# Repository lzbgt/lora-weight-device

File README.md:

# Hospital Urine Bag Monitoring System (LoRaWAN)

## Project Overview
A low-power, connected IoT device designed to automatically monitor urine output in hospital wards. It replaces manual visual checks with real-time digital logging, improving patient care and reducing nurse workload.

**Key Features:**
*   **Sensing:** Weight-based (Load Cell) for non-contact, universal bag compatibility.
*   **Connectivity:** **LoRaWAN** (Sub-1GHz) for deep indoor penetration and low infrastructure cost (1 gateway per ward).
*   **Battery Life:** Multi-year operation on AA batteries or Li-SoCl2.
*   **User Interface:** E-Ink Display for always-on visibility and local "Tare" button.
*   **Infrastructure:** Supports both **PoE** and **Wi-Fi** backhaul for the Gateway.

## Repository Structure

### Design Documents (`design_docs/`)
*   **`system_architecture.md`**: High-level topology, data flow, and server stack (ChirpStack).
*   **`hardware_design.md`**: Schematic concepts, chip selection (RAK3172, HX711), and detailed pin mapping.
*   **`mechanical_design.md`**: Enclosure styling, IP65 sealing, and the miniature load cell integration (Hook mechanism).
*   **`firmware_design.md`**: Software logic, state machine (Deep Sleep), and LoRaWAN payload format.
*   **`pcb_layout_guide.md`**: Critical routing rules for RF impedance and Analog noise reduction.
*   **`detailed_bom.md`**: Bill of Materials with part numbers and cost estimates.
*   **`solution_proposal.md`**: original proposal.

### Datasheets (`datasheets/`)
Contains reference specifications for critical components:
*   **RAK3172**: LoRaWAN Module.
*   **GDEY0213B74**: 2.13" E-Ink Display.
*   **HX711**: 24-Bit ADC.
*   **SSD1680**: Display Controller (Command Table).

## Getting Started

### 1. Hardware Development
*   Review `hardware_design.md` for the schematic connectivity.
*   Follow `pcb_layout_guide.md` for board layout, paying special attention to the **50Ω RF Trace** and **E-Ink Booster** loop.
*   Ensure the **Schottky Diode OR-ing** is implemented to protect the 3.3V rail.

### 2. Firmware Development
*   **Toolchain:** STM32CubeWL SDK + CMake + GCC ARM.
*   **Key Logic:** Implement the "Deep Sleep Loop" (Wait 400ms for HX711 -> Read -> Sleep).
*   **Display:** Use the SSD1680 driver with the specific bias voltages (+20V/-20V/+15V/-15V) defined in the hardware spec.

### 3. Mechanical Prototyping
*   Design the enclosure to fit the **Miniature Load Cell** (40mm).
*   Ensure the **Tube Retention Clip** is molded into the front shell to prevent measurement errors.

## License
Proprietary / Internal Company Use.

## Commercial support

For teams adapting this repo for ESP32, Bluetooth, Wi-Fi provisioning, LoRa/LoRaWAN, low-power sensing, gateway handoff, or prototype-to-pilot embedded device work, I offer a paid bring-up review:

- Review page: https://x2.brucelu.top/iot/?source=github-lora-weight-device
- Sample deliverable: https://x2.brucelu.top/iot/sample/
- Checkout: https://x2.brucelu.top/iot/checkout/?source=github-lora-weight-device
- Product catalog: https://x2.brucelu.top/products/?source=github-lora-weight-device

Boundary: this is paid engineering review/support. It does not include medical/regulatory approval, guaranteed RF range, hardware repair, credential-managed operation, or custom firmware delivery.

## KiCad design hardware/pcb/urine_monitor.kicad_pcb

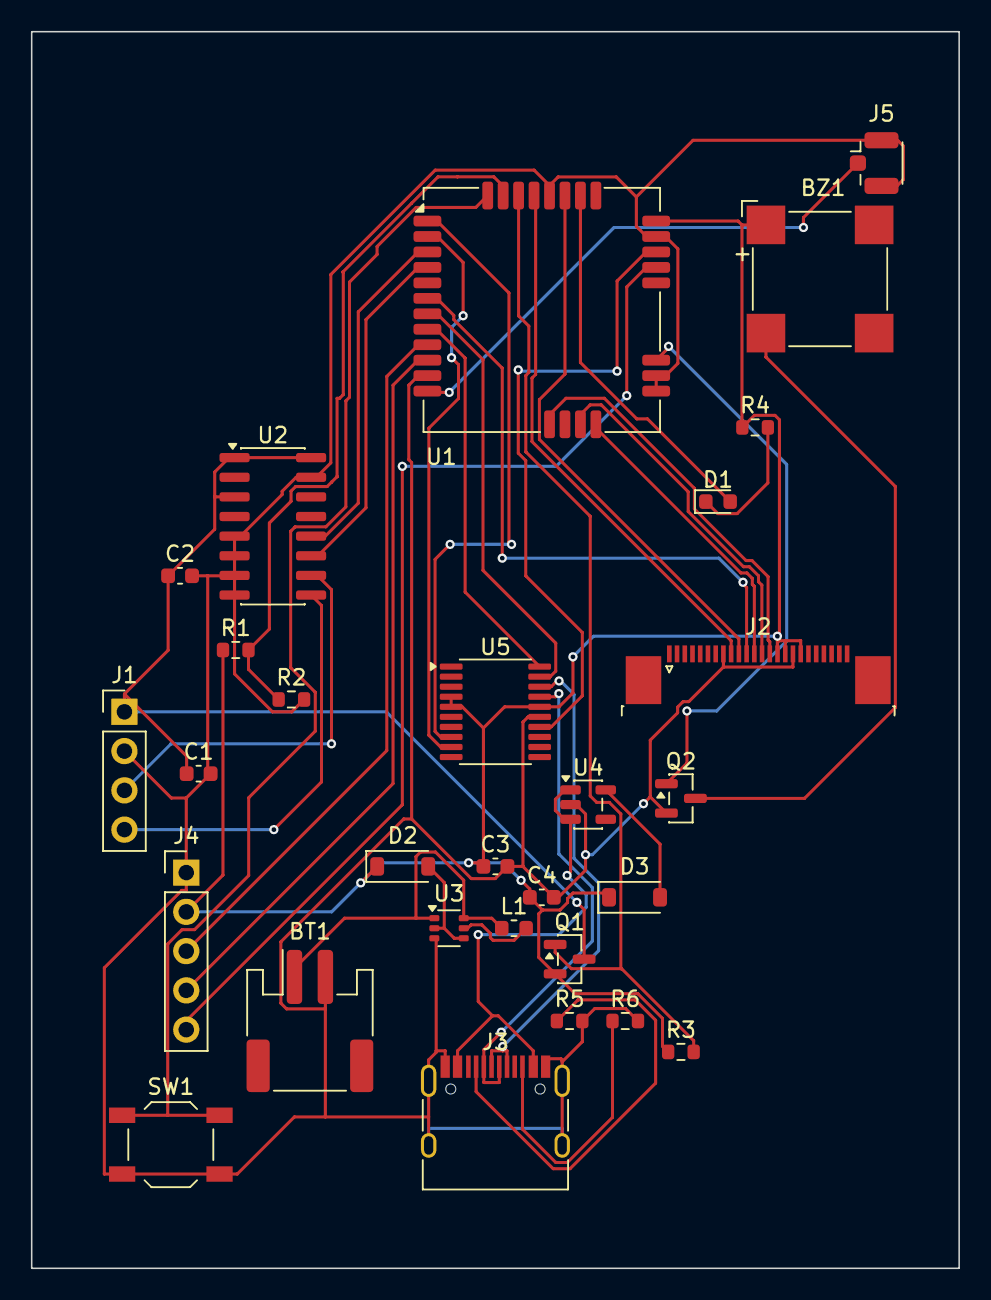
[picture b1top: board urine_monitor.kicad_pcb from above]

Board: 2 copper layers, 60.0 x 80.0 mm, 29 parts (0 on the bottom side), 38 nets.

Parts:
BT1: BAT_JST; JST_PH_S2B-PH-SM4-TB_1x02-1MP_P2.00mm_Horizontal
BZ1: Buzzer; MagneticBuzzer_CUI_CMT-8504-100-SMT
C1, C3: 10uF; C_0603_1608Metric
C2, C4: 0.1uF; C_0603_1608Metric
D1: RED; LED_0603_1608Metric
D2, D3: SS14; D_SOD-123
J1: LoadCell; PinHeader_1x04_P2.54mm_Vertical
J2: EInk_FPC; TE_2-1734839-4_1x24-1MP_P0.5mm_Horizontal
J3: USB-C_Dev; USB_C_Receptacle_HRO_TYPE-C-31-M-12
J4: I2C+BOOT0+PWR; PinHeader_1x05_P2.54mm_Vertical
J5: Antenna_UFL; U.FL_Hirose_U.FL-R-SMT-1_Vertical
L1: 4.7uH; L_0603_1608Metric
Q1: SI2301; SOT-23
Q2: 2N7002; SOT-23
R1, R2: 1M; R_0603_1608Metric
R3: 100k; R_0603_1608Metric
R4: 1k; R_0603_1608Metric
R5, R6: 5k1; R_0603_1608Metric
SW1: USER_BTN; SW_SPST_TL3342
U1: RAK3172
U2: HX711; SOIC-16_3.9x9.9mm_P1.27mm
U3: TPS61220; SOT-363_SC-70-6
U4: MIC5504-3.3; SOT-23-5
U5: STM32F042F6P6 (USB CDC + CMSIS-DAP); TSSOP-20_4.4x6.5mm_P0.65mm

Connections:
BAT: BT1.1, L1.1, U3.1, U3.6
BAT_SENSE: R1.2, R2.1, U1.31
BOOT0: J4.5, U1.21
BTN_USER: SW1.1, U1.32
BUZZ_PWM: Q2.1, U1.19
BUZZ_SINK: BZ1.2, Q2.3
CC1: J3.A5, R5.1
CC2: J3.B5, R6.1
EINK_BUSY: J2.9, U1.29
EINK_CS: J2.12, U1.16
EINK_DC: J2.11, U1.6
EINK_MOSI: J2.14, U1.13
EINK_RST: J2.10, U1.27
EINK_SCK: J2.13, U1.15
GND: BT1.2, C1.2, C2.2, C3.2, C4.2, J1.2, J2.8, J2.17, J3.A1, J3.A12, J3.B1, J3.B12, J3.S1, J4.1, J5.2, Q2.2, R2.2, R5.2, R6.2, SW1.2, U1.11, U1.17, U1.18, U1.23, U1.28, U2.5, U2.6, U2.7, U2.8, U2.15, U3.3, U4.2, U5.15
HX711_DT: U1.3, U2.12
HX711_SCK: U1.4, U2.11
HX_GATE: Q1.1, R3.2, U1.30
HX_INB+: J1.3, U2.10
HX_INB-: J1.4, U2.9
HX_VCC: C1.1, C2.1, J1.1, Q1.3, U2.1, U2.3, U2.16
I2C_SCL: J4.3, U1.9
I2C_SDA: J4.4, U1.10
LED_NET: D1.1, R4.2
LED_STATUS: D1.2, U1.26
NRST: U1.22, U5.14
RF: J5.1, U1.12
SWCLK: U1.8, U5.20
SWDIO: U1.7, U5.19
U3_L: L1.2, U3.5
U3_OUT: D2.2, U3.2, U3.4
U4_OUT: D3.2, U4.5
UART2_RX: U1.1, U5.8
UART2_TX: U1.2, U5.9
USB_DM: J3.A7, J3.B7, U5.17
USB_DP: J3.A6, J3.B6, U5.18
VBUS: J3.A4, J3.A9, J3.B4, J3.B9, U4.1, U4.3
VCC: BZ1.1, C3.1, C4.1, D2.1, D3.1, J2.15, J2.16, J2.18, J4.2, Q1.2, R1.1, R3.1, R4.1, U1.24, U5.4, U5.5, U5.16

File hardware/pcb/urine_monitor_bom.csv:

"Refs","Value","Footprint","Qty","DNP"
"BT1","BAT_JST","Connector_JST:JST_PH_S2B-PH-SM4-TB_1x02-1MP_P2.00mm_Horizontal","1",""
"BZ1","Buzzer","Buzzer_Beeper:MagneticBuzzer_CUI_CMT-8504-100-SMT","1",""
"C1","10uF","Capacitor_SMD:C_0603_1608Metric","1",""
"C2","0.1uF","Capacitor_SMD:C_0603_1608Metric","1",""
"C3","10uF","Capacitor_SMD:C_0603_1608Metric","1",""
"C4","0.1uF","Capacitor_SMD:C_0603_1608Metric","1",""
"D1","RED","LED_SMD:LED_0603_1608Metric","1",""
"D2","SS14","Diode_SMD:D_SOD-123","1",""
"D3","SS14","Diode_SMD:D_SOD-123","1",""
"J1","LoadCell","Connector_PinHeader_2.54mm:PinHeader_1x04_P2.54mm_Vertical","1",""
"J2","EInk_FPC","Connector_FFC-FPC:TE_2-1734839-4_1x24-1MP_P0.5mm_Horizontal","1",""
"J3","USB-C_Dev","Connector_USB:USB_C_Receptacle_HRO_TYPE-C-31-M-12","1",""
"J4","I2C+BOOT0+PWR","Connector_PinHeader_2.54mm:PinHeader_1x05_P2.54mm_Vertical","1",""
"J5","Antenna_UFL","Connector_Coaxial:U.FL_Hirose_U.FL-R-SMT-1_Vertical","1",""
"L1","4.7uH","Inductor_SMD:L_0603_1608Metric","1",""
"Q1","SI2301","Package_TO_SOT_SMD:SOT-23","1",""
"Q2","2N7002","Package_TO_SOT_SMD:SOT-23","1",""
"R1","1M","Resistor_SMD:R_0603_1608Metric","1",""
"R2","1M","Resistor_SMD:R_0603_1608Metric","1",""
"R3","100k","Resistor_SMD:R_0603_1608Metric","1",""
"R4","1k","Resistor_SMD:R_0603_1608Metric","1",""
"R5","5k1","Resistor_SMD:R_0603_1608Metric","1",""
"R6","5k1","Resistor_SMD:R_0603_1608Metric","1",""
"SW1","USER_BTN","Button_Switch_SMD:SW_SPST_TL3342","1",""
"U1","RAK3172","RF_Module:RAK3172","1",""
"U2","HX711","Package_SO:SOIC-16_3.9x9.9mm_P1.27mm","1",""
"U3","TPS61220","Package_TO_SOT_SMD:SOT-363_SC-70-6","1",""
"U4","MIC5504-3.3","Package_TO_SOT_SMD:SOT-23-5","1",""
"U5","STM32F042F6P6 (USB CDC + CMSIS-DAP)","Package_SO:TSSOP-20_4.4x6.5mm_P0.65mm","1",""

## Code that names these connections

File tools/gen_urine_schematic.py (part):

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add("VCC", "U5", "5")  # VDDA
add("GND", "U5", "15")  # VSSA
add("VCC", "U5", "4")  # NRST pulled high (simple strap)
add("USB_DM", "U5", "17")  # PA11
add("USB_DP", "U5", "18")  # PA12
add("SWDIO", "U5", "19")  # PA13 -> target SWDIO
add("SWCLK", "U5", "20")  # PA14 -> target SWCLK
add("NRST", "U5", "14")  # PB1 drives target NRST
add("UART2_RX", "U5", "8")  # PA2 TX -> target RX
add("UART2_TX", "U5", "9")  # PA3 RX <- target TX

# USB bridge decoupling
add("VCC", "C4", "1")
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
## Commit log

2025-12-07 init
2025-12-09 v0.0.2
2026-05-17 Add Embedded IoT bring-up review link
2026-05-17 Add paid support funding link
2026-05-17 Add paid support guide
2026-05-17 Add paid support issue contact links
2026-05-17 Add paid support badges
2026-05-18 Remove repo advertising surface
2026-05-18 Remove repo advertising links
2026-05-18 Replace advertising links with neutral donation link
